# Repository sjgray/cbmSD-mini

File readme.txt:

cbmSD-mini - SD Card Drive for Commodore Computers with IEEE
============================================================

The goal of this project is to create a free open-source
disk drive solution that is easy to build using all
thru-hole parts plus the use of a common inexpensive SD
card module.

This device is based on the petSD+ v2.4 from Nils Eilers.
I have removed all the non-essential features and have
designed it to plug directly into the back of the computer.
No IEEE cables are required. However, it also has a
pass-thru to add additional drives if you need.

You will need a simple cassette port power plug or you can
power it with a standard 5V adapter with barrel jack.

Features
--------

- Direct plug into IEEE port
- Pass-thru IEEE port
- Power, Busy and Error lights
- SD module can be mounted on header or extended via wires.
- Reset switch.
- Two Power headers for input or output (to additional
  cbmSD-mini units).
- Mounting holes for future 3D case.

Project Page
------------

http://www.cbmsteve.ca/cbmsd/index.html

Status
------

 cbmSD      1.0:  Was the first version for prototyping. It supported IEEE and IEC
                  like the PETSD+. 
 cbmSD-mini 1.1:  Removed IEC port and AUX header. IEEE only for PET/CBM users.
                  Gerbers sent to JLCPCB on 2021-05-14.
 cbmSD-mini 1.2:  Fix trace short on LED. Remove 74125 which is not reqired
                  for IEEE. Update design for Kicad7.
                  Gerbers sent to JLCPCB on 2024-02-21.
 cmmSD-mini 1.2v  Add vertical mounting option.
                  Gerbers sent to JLCPCB on 2024-07-30.

Steve
2024-11-11

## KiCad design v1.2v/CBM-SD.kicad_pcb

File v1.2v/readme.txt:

cbmSD-mini - SD Card Drive for Commodore Computers with IEEE
============================================================

**NEW** Webpage: http://cbmsteve.ca/cbmsd/index.html

The goal of this project is to create a free open-source
disk drive solution that is easy to build using all
thru-hole parts plus the use of a common inexpensive SD
card module.

This device is based on the petSD+ v2.4 from Nils Eilers.
I have removed all the non-essential features and have
designed it to plug directly into the back of the computer.
No IEEE cables are required. However, it also has a
pass-thru to add additional drives if you need.

You will need a simple cassette port power plug or you can
power it with a standard 5V adapter with barrel jack.

Features
--------

- Direct plug into IEEE port
- Pass-thru IEEE port
- Power, Busy and Error lights
- SD module can be mounted on header or extended via wires.
- Reset switch.
- Two Power headers for input or output (to additional
  cbmSD-mini units.
- Mounting holes for future 3D case.
- Vertical mounting option

Status
------

 V1.0: Was the first version for prototyping. It had a few errors.       
 V1.1: Removed IEC port and AUX header. IEEE only for PET/CBM users.
       Gerbers sent to JLCPCB on 2021-05-14.
 V1.2: Fix trace short on LED. Remove 74125 which is not required
       for IEEE. Update design for Kicad7.
 V1.2v: No fundamental changes. Moved some parts to make way for
        vertical mounting option.

Steve
2024-02-21

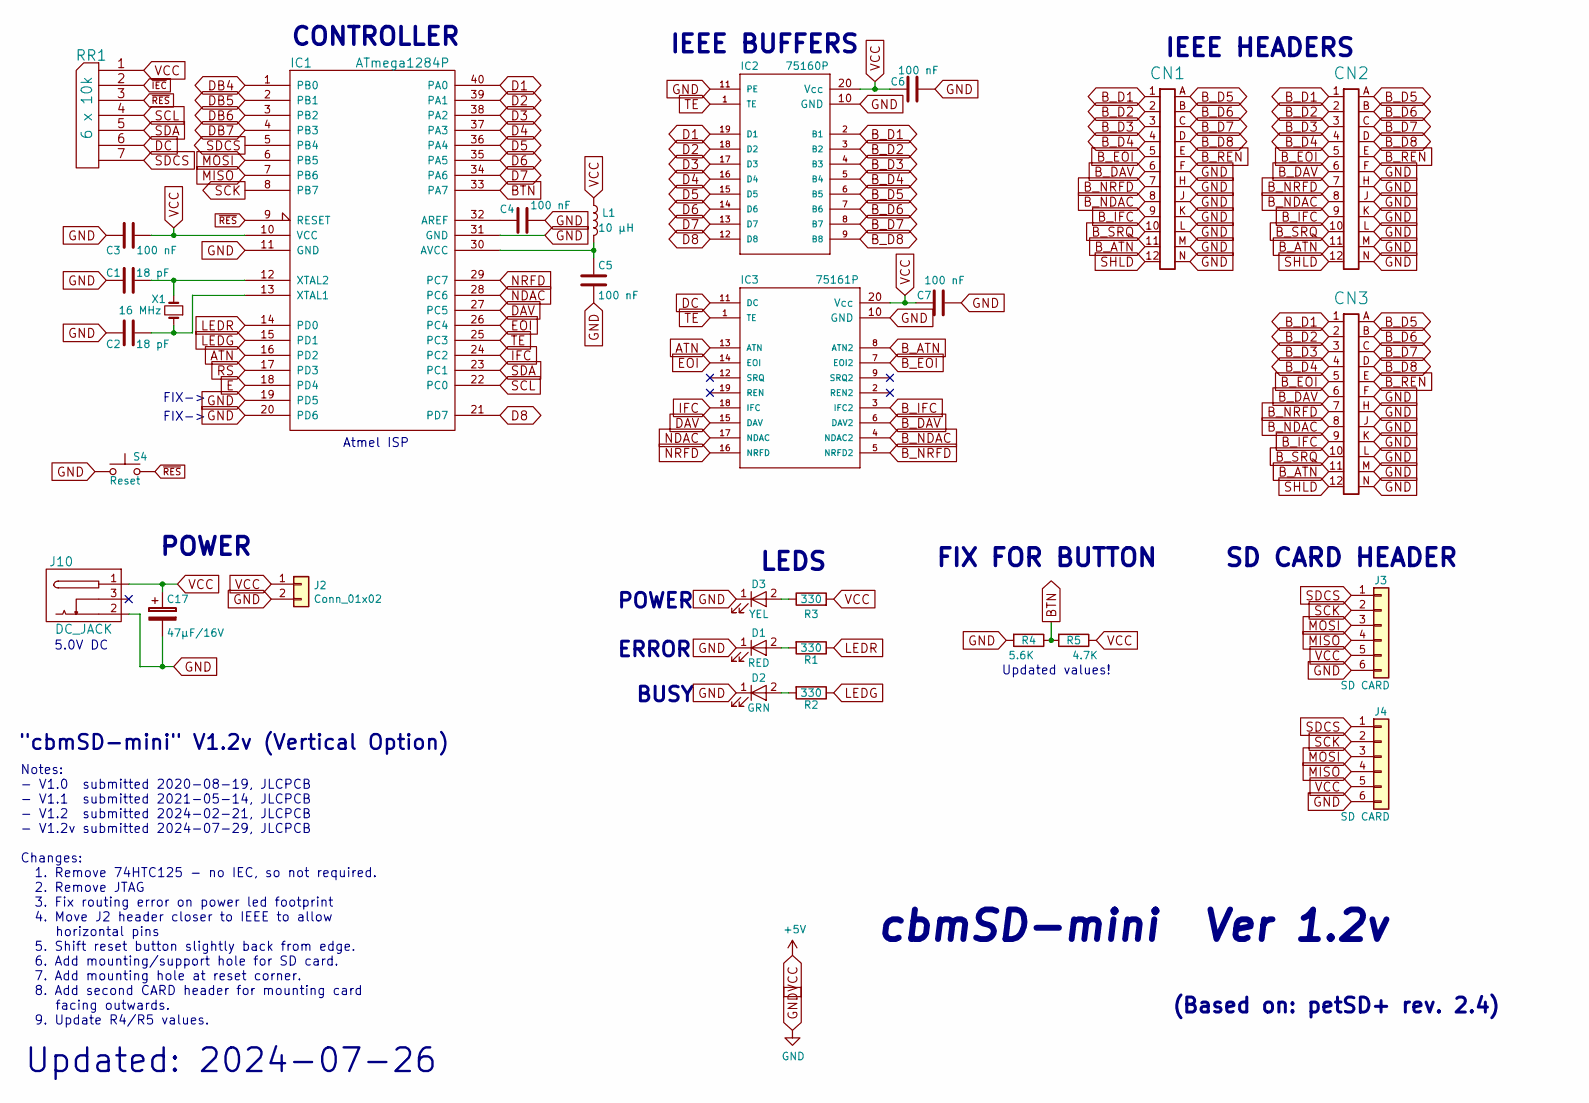
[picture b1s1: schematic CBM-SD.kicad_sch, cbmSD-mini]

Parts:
C1, C2: 18 pF; C_Disc_D3.8mm_W2.6mm_P2.50mm
C3, C4, C5, C6, C7: 100 nF; C_Disc_D3.8mm_W2.6mm_P2.50mm
C17: 47µF/16V; CP_Radial_D6.3mm_P2.50mm
CN1, CN2: EDGE_CON_02x12; EDGE_CON_24P
CN3: EDGE_CON_02x12; EDGE_02x12-VERTICAL_THT
D1: RED; LED_D3.0mm_Clear
D2: GRN; LED_D3.0mm_Clear
D3: YEL; LED_D3.0mm_Clear
IC1: ATmega1284P; DIP-40_W15.24mm
IC2: 75160P; DIP-20_W7.62mm
IC3: 75161P; DIP-20_W7.62mm
J2: Conn_01x02; PinHeader_1x02_P2.54mm_Vertical
J3, J4: SD CARD; PinHeader_1x06_P2.54mm_Vertical
J10: DC_JACK; BarrelJack_Horizontal
L1: 10 µH; L_Axial_L7.0mm_D3.3mm_P10.16mm_Horizontal_Fastron_MICC
R1, R2, R3: 330; R_Axial_DIN0207_L6.3mm_D2.5mm_P10.16mm_Horizontal
R4: 5.6K; R_Axial_DIN0207_L6.3mm_D2.5mm_P10.16mm_Horizontal
R5: 4.7K; R_Axial_DIN0207_L6.3mm_D2.5mm_P10.16mm_Horizontal
RR1: 6 x 10k; R_Array_SIP7
S4: Reset; SW_Tactile_SKHH_Angled
X1: 16 MHz; Crystal_HC49-4H_Vertical

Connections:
ATN: IC1.16 (PD2), IC3.13 (ATN)
BTN: IC1.33 (PA7), R4.1, R5.2
B_ATN: CN1.11, CN2.11, CN3.11, IC3.8 (ATN2)
B_D1: CN1.1, CN2.1, CN3.1, IC2.2 (B1)
B_D2: CN1.2, CN2.2, CN3.2, IC2.3 (B2)
B_D3: CN1.3, CN2.3, CN3.3, IC2.4 (B3)
B_D4: CN1.4, CN2.4, CN3.4, IC2.5 (B4)
B_D5: CN1.A, CN2.A, CN3.A, IC2.6 (B5)
B_D6: CN1.B, CN2.B, CN3.B, IC2.7 (B6)
B_D7: CN1.C, CN2.C, CN3.C, IC2.8 (B7)
B_D8: CN1.D, CN2.D, CN3.D, IC2.9 (B8)
B_DAV: CN1.6, CN2.6, CN3.6, IC3.6 (DAV2)
B_EOI: CN1.5, CN2.5, CN3.5, IC3.7 (EOI2)
B_IFC: CN1.9, CN2.9, CN3.9, IC3.3 (IFC2)
B_NDAC: CN1.8, CN2.8, CN3.8, IC3.4 (NDAC2)
B_NRFD: CN1.7, CN2.7, CN3.7, IC3.5 (NRFD2)
B_REN: CN1.E, CN2.E, CN3.E
B_SRQ: CN1.10, CN2.10, CN3.10
D1: IC1.40 (PA0), IC2.19 (D1)
D2: IC1.39 (PA1), IC2.18 (D2)
D3: IC1.38 (PA2), IC2.17 (D3)
D4: IC1.37 (PA3), IC2.16 (D4)
D5: IC1.36 (PA4), IC2.15 (D5)
D6: IC1.35 (PA5), IC2.14 (D6)
D7: IC1.34 (PA6), IC2.13 (D7)
D8: IC1.21 (PD7), IC2.12 (D8)
DAV: IC1.27 (PC5), IC3.15 (DAV)
DB4: IC1.1 (PB0)
DB5: IC1.2 (PB1)
DB6: IC1.3 (PB2)
DB7: IC1.4 (PB3)
DC: IC3.11 (DC), RR1.6
E: IC1.18 (PD4)
EOI: IC1.26 (PC4), IC3.14 (EOI)
GND: C1.1, C2.1, C3.1, C4.2, C5.2, C6.1, C7.1, C17.2, CN1.F, CN1.H, CN1.J, CN1.K, CN1.L, CN1.M, CN1.N, CN2.F, CN2.H, CN2.J, CN2.K, CN2.L, CN2.M, CN2.N, CN3.F, CN3.H, CN3.J, CN3.K, CN3.L, CN3.M, CN3.N, D1.1 (K), D2.1 (K), D3.1 (K), IC1.11 (GND), IC1.19 (PD5), IC1.20 (PD6), IC1.31 (GND), IC2.10 (GND), IC2.11 (PE), IC3.10 (GND), J2.2, J3.6, J4.6, J10.2, R4.2, S4.1
IFC: IC1.24 (PC2), IC3.18 (IFC)
LEDG: IC1.15 (PD1), R2.1
LEDR: IC1.14 (PD0), R1.1
MISO: IC1.7 (PB6), J3.4, J4.4
MOSI: IC1.6 (PB5), J3.3, J4.3
NDAC: IC1.28 (PC6), IC3.17 (NDAC)
NRFD: IC1.29 (PC7), IC3.16 (NRFD)
unnamed: D1.2 (A), R1.2
unnamed: D2.2 (A), R2.2
unnamed: D3.2 (A), R3.1
unnamed: C4.1, IC1.32 (AREF)
unnamed: C5.1, IC1.30 (AVCC), L1.2
unnamed: C2.2, IC1.13 (XTAL1), X1.1
unnamed: C1.2, IC1.12 (XTAL2), X1.2
RS: IC1.17 (PD3)
SCK: IC1.8 (PB7), J3.2, J4.2
SCL: IC1.22 (PC0), RR1.4
SDA: IC1.23 (PC1), RR1.5
SDCS: IC1.5 (PB4), J3.1, J4.1, RR1.7
SHLD: CN1.12, CN2.12, CN3.12
TE: IC1.25 (PC3), IC2.1 (TE), IC3.1 (TE)
VCC: C3.2, C6.2, C7.2, C17.1, IC1.10 (VCC), IC2.20 (Vcc), IC3.20 (Vcc), J2.1, J3.5, J4.5, J10.1, L1.1, R3.2, R5.1, RR1.1 (COM)
~IEC: RR1.2
~RES: IC1.9 (RESET), RR1.3, S4.2

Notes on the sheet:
Updated values!
5.0V DC
BUSY
Notes: - V1.0 submitted 2020-08-19, JLCPCB - V1.1 submitted 2021-05-14, JLCPCB - V1.2 submitted 2024-02-21, JLCPCB - V1.2v submitted 2024-07-29, JLCPCB Changes: 1. Remove 74HTC125 - no IEC, so not required. 2. Remove JTAG 3. Fix routing error on power led footprint 4. Move J2 header closer to IEEE 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
Atmel ISP
"cbmSD-mini" V1.2v (Vertical Option)
FIX FOR BUTTON
SD CARD HEADER
cbmSD-mini Ver 1.2v
CONTROLLER
IEEE HEADERS
(Based on: petSD+ rev. 2.4)
FIX->
POWER
LEDS
ERROR
Updated: 2024-07-26
IEEE BUFFERS

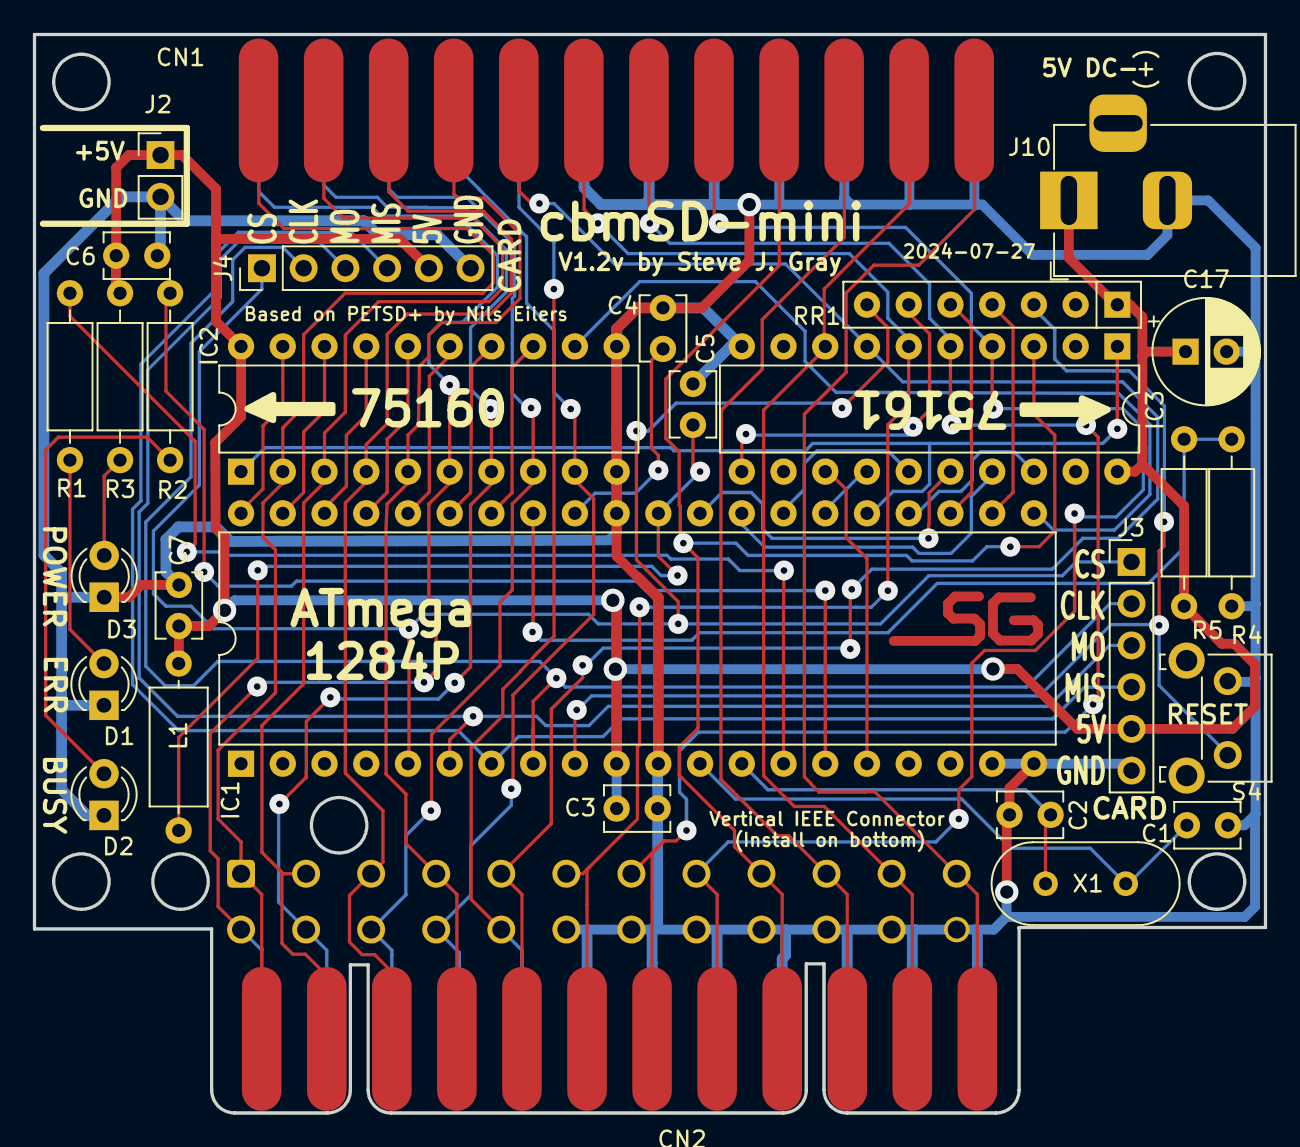
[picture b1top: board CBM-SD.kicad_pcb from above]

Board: 2 copper layers, 74.9 x 65.6 mm, 30 parts (1 on the bottom side), 52 nets.

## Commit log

2021-05-15 :tada: Added .gitattributes & .gitignore files
2021-05-15 V1.1 Initial commit
    Initial commit. Boards have been ordered but not verified. See webpage
    for info.
2024-02-21 cbmSD-mini V1.2 Release
    Released V1.2 with Gerbers. This is mostly a cleanup of V1.1 with 74125 removed. Updated for Kicad7. Version 1.1 and 1.2 are in separate directories now.
2024-02-21 Add readme to root
    Add readme
2024-03-18 V1.2 verified
    Board built and is working correctly!
2024-03-21 Update CBM-SD.pdf
    Fix R4/R5 values.
2024-06-01 Update Weblink
    Update link to new project webpage.
2024-06-01 Add Interactive BOM
    Add interactive BOM
2024-11-11 Version 1.2v Release
    Moved a few components and added vertical mounting option.
2024-11-11 Update readme
    Add 1.2v

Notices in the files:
v1.2/CBM-SD.kicad_sch:
Schematic and PCB layout licensed under CC-BY-SA 4.0
